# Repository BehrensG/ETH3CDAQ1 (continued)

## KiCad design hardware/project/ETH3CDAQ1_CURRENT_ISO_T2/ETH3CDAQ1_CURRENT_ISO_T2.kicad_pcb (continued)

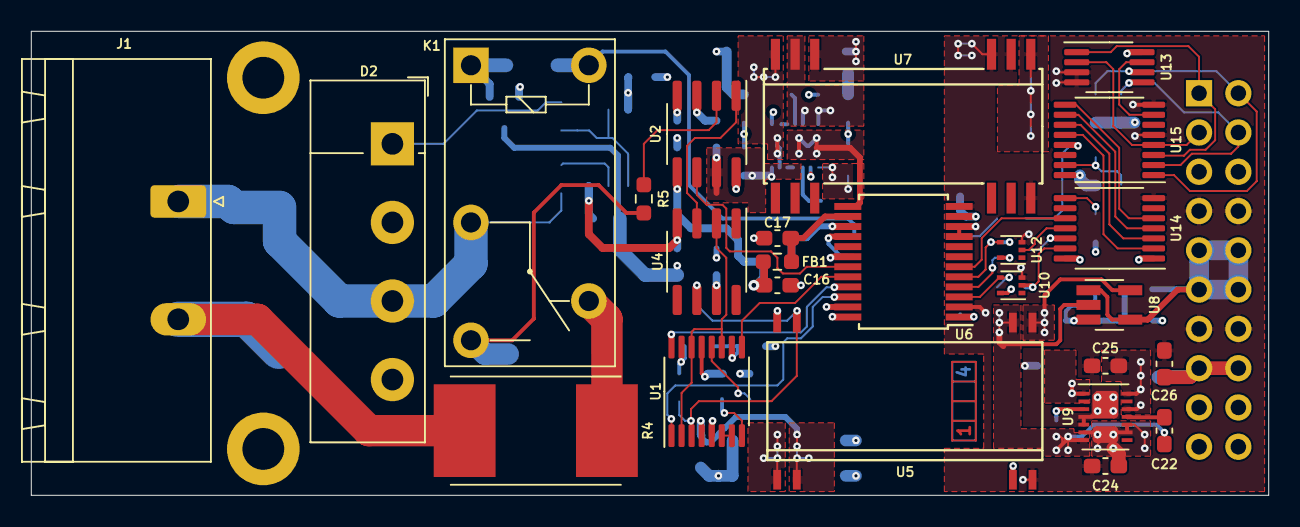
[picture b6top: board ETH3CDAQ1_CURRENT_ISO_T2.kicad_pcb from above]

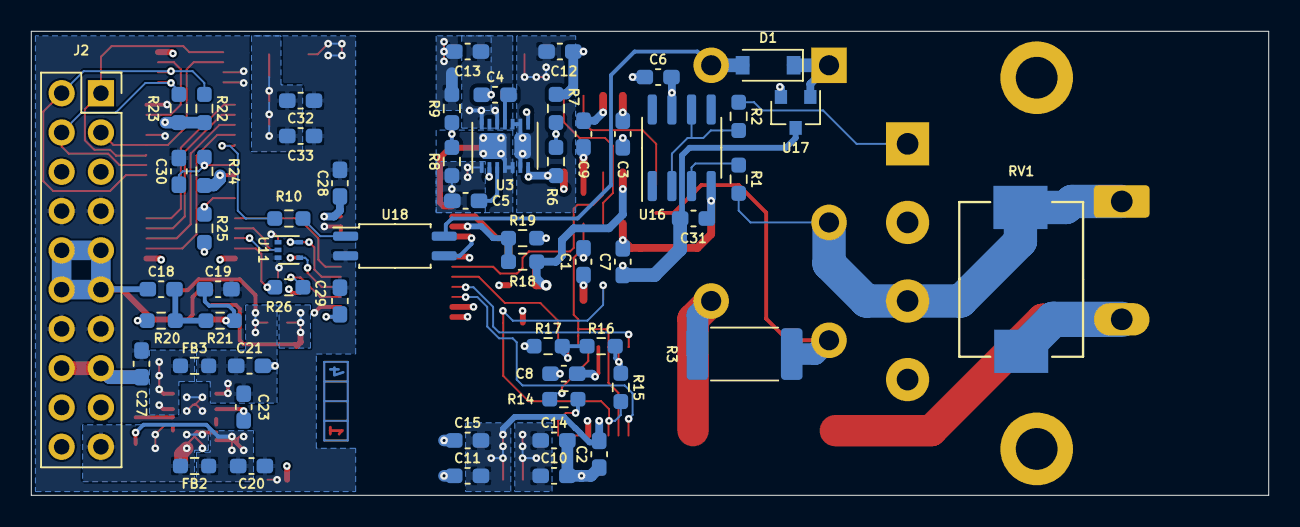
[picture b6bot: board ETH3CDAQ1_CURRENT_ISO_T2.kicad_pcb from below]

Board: 4 copper layers, 80.0 x 30.0 mm, 85 parts (58 on the bottom side), 65 nets.

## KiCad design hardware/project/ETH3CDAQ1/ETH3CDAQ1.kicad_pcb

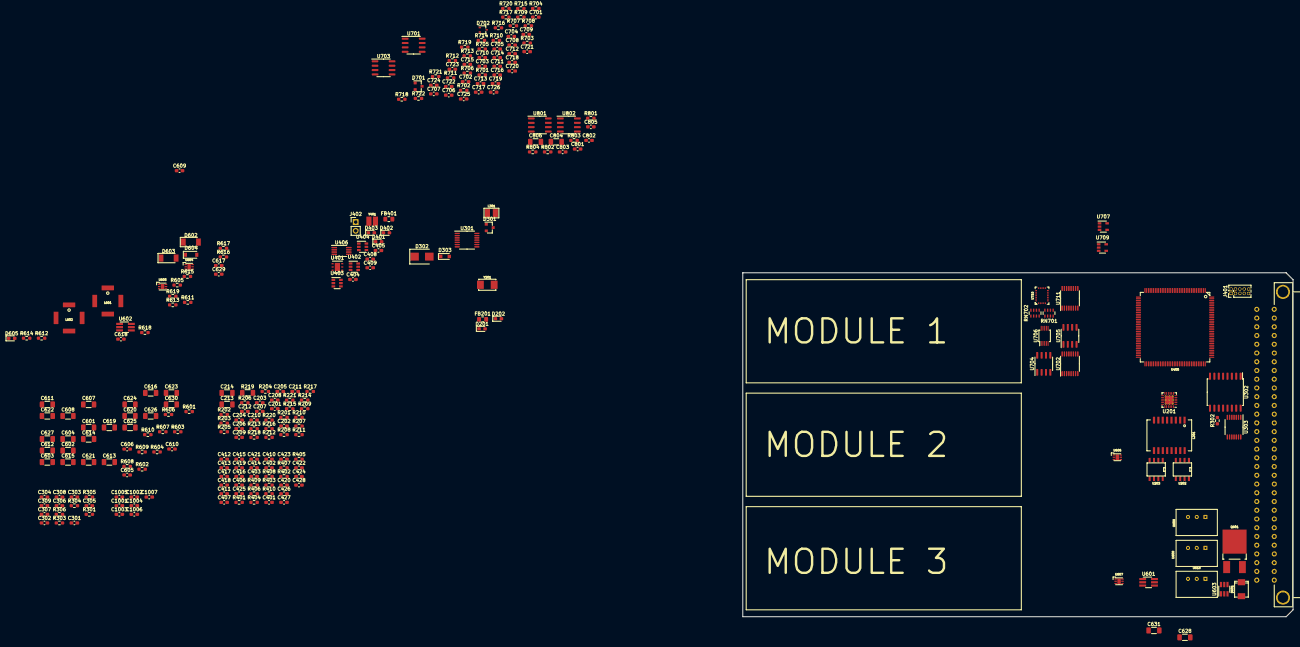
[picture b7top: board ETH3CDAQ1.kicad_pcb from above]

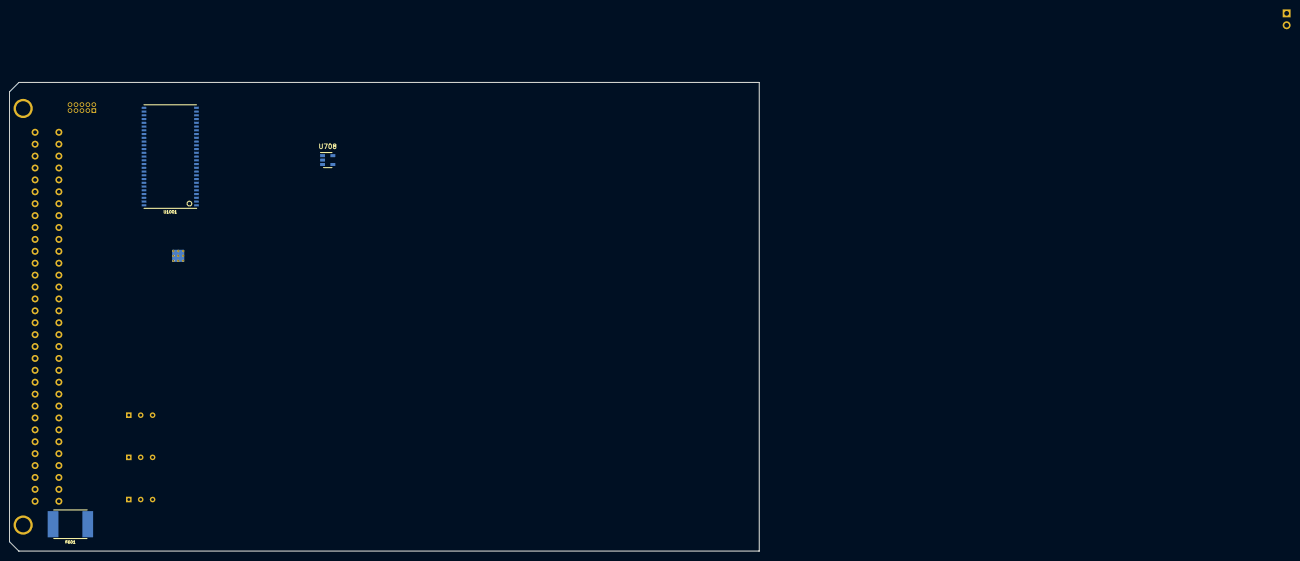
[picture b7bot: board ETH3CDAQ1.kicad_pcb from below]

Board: 4 copper layers, 160.0 x 100.0 mm, 269 parts (3 on the bottom side), 207 nets, no tracks yet.

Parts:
C201, C204, C404, C405: 8p; C_0603_1608Metric_Pad1.08x0.95mm_HandSolder
C202, C205, C208, C209, C210, C211, C212, C301, C303, C304, C306, C308, C401, C402, C403, C406, C407, C411, C412, C413, C414, C415, C416, C417, C418, C419, C420, C421, C422, C423, C424, C425, C426, C428, C617, C618, C629, C701, C702, C703, C704, C705, C706, C707, C708, C709, C710, C712, C713, C714, C715, C717, C718, C719, C720, C722, C801, C802, C803, C805, C1001, C1002, C1003, C1004, C1005, C1006, C1007: 100n; C_0603_1608Metric_Pad1.08x0.95mm_HandSolder
C203: 470p; C_0603_1608Metric_Pad1.08x0.95mm_HandSolder
C206, C207, C302, C305, C307, C410, C427, C605, C606: 1u; C_0603_1608Metric_Pad1.08x0.95mm_HandSolder
C213, C214: 1n/1kV; C_1206_3216Metric_Pad1.33x1.80mm_HandSolder
C309, C724: 47p; C_0603_1608Metric_Pad1.08x0.95mm_HandSolder
C408, C409, C723: 2u2; C_0603_1608Metric_Pad1.08x0.95mm_HandSolder
C601, C602, C615, C616, C623, C624, C628: 10u/50V; C_1206_3216Metric_Pad1.33x1.80mm_HandSolder
C603, C604, C611, C612, C613, C614: 4u7/50V; C_1206_3216Metric_Pad1.33x1.80mm_HandSolder
C607, C608: 1u/HC; C_1206_3216Metric_Pad1.33x1.80mm_HandSolder
C609, C610: 4p7; C_0603_1608Metric_Pad1.08x0.95mm_HandSolder
C619, C620: 10u/35V; C_1206_3216Metric_Pad1.33x1.80mm_HandSolder
C621: 4u7/25V; C_1206_3216Metric_Pad1.33x1.80mm_HandSolder
C622, C804, C806: 10u; C_1206_3216Metric_Pad1.33x1.80mm_HandSolder
C625, C626, C630, C631: 10u/16V; C_1206_3216Metric_Pad1.33x1.80mm_HandSolder
C627: 4u7; C_1206_3216Metric_Pad1.33x1.80mm_HandSolder
C711: 330p; C_0603_1608Metric_Pad1.08x0.95mm_HandSolder
C716: 100p; C_0603_1608Metric_Pad1.08x0.95mm_HandSolder
C721: 1000p; C_0603_1608Metric_Pad1.08x0.95mm_HandSolder
C725, C726: C; C_0603_1608Metric_Pad1.08x0.95mm_HandSolder
D201: YELLOW; LED_0603_1608Metric_Pad1.05x0.95mm_HandSolder
D202, D402: GREEN; LED_0603_1608Metric_Pad1.05x0.95mm_HandSolder
D301: BAV99; SOT-23
D302: SMBJ5.0A; D_SMB
D303: SD36C-01FTG; D_SOD-323_HandSoldering
D401, D605: RED; LED_0603_1608Metric_Pad1.05x0.95mm_HandSolder
D403: BLUE; LED_0603_1608Metric_Pad1.05x0.95mm_HandSolder
D601: SM6T30AY; DO_214AA_REV
D602, D603: PMEG6010EP,115; D_SOD-128
D604: MMSZ5249B; D_SOD-123
D701: MMBZ15VDL; SOT-23
D702: BAT54SW; SOT-323_SC-70
F601: MF-LSMF185/33X; Fuse_SMD2920
FB201, FB401: 742792031; L_0805_2012Metric_Pad1.15x1.40mm_HandSolder
J401: 20021111-00010T4LF; PinHeader_2x05_P1.27mm_Vertical
J402: Conn_02x01; PinHeader_1x02_P2.54mm_Vertical
J501: C64AC; Socket_DIN41612-CaseC1-AC-Male-64Pin-2rows
L201: 749010012A
L301: CW252016-R33G; CW252016
L601, L602: 74489440068
Q601: IRFR5410; TO-252-2_Rectifier
R201, R202, R204, R205: 33; R_0603_1608Metric_Pad0.98x0.95mm_HandSolder
R203, R206, R207, R208, R209, R211, R301, R408, R409, R410, R705, R706, R707, R801, R802, R804: 10k; R_0603_1608Metric_Pad0.98x0.95mm_HandSolder
R210: 1k5; R_0603_1608Metric_Pad0.98x0.95mm_HandSolder
R212: 12k1; R_0603_1608Metric_Pad0.98x0.95mm_HandSolder
R213, R214: 270; R_0603_1608Metric_Pad0.98x0.95mm_HandSolder
R215, R216, R217, R218: 49R9; R_0603_1608Metric_Pad0.98x0.95mm_HandSolder
R219: 1M/1kV; R_1206_3216Metric_Pad1.30x1.75mm_HandSolder
R220, R221: 75/1%; R_0603_1608Metric_Pad0.98x0.95mm_HandSolder
R302: 14k7; R_0603_1608Metric_Pad0.98x0.95mm_HandSolder
R303: 100; R_0603_1608Metric_Pad0.98x0.95mm_HandSolder
R304: 1k; R_0603_1608Metric_Pad0.98x0.95mm_HandSolder
R305: 47; R_0603_1608Metric_Pad0.98x0.95mm_HandSolder
R306: 51R1; R_0603_1608Metric_Pad0.98x0.95mm_HandSolder
R401, R402, R406, R407: 4k7; R_0603_1608Metric_Pad0.98x0.95mm_HandSolder
R403, R405: 680; R_0603_1608Metric_Pad0.98x0.95mm_HandSolder
R404: 560; R_0603_1608Metric_Pad0.98x0.95mm_HandSolder
R601, R603, R606, R608: 1M; R_0603_1608Metric_Pad0.98x0.95mm_HandSolder
R602, R604: 287k; R_0603_1608Metric_Pad0.98x0.95mm_HandSolder
R605, R611: 100k; R_0603_1608Metric_Pad0.98x0.95mm_HandSolder
R607: 111k; R_0603_1608Metric_Pad0.98x0.95mm_HandSolder
R609: 53k; R_0603_1608Metric_Pad0.98x0.95mm_HandSolder
R610: 370; R_0603_1608Metric_Pad0.98x0.95mm_HandSolder
R612, R618: 49k9; R_0603_1608Metric_Pad0.98x0.95mm_HandSolder
R613: 150k; R_0603_1608Metric_Pad0.98x0.95mm_HandSolder
R614: 13k3; R_0603_1608Metric_Pad0.98x0.95mm_HandSolder
R615, R616, R619: R; R_0603_1608Metric_Pad0.98x0.95mm_HandSolder
R617: 25k; R_0603_1608Metric_Pad0.98x0.95mm_HandSolder
R701, R704, R714: 0; R_0603_1608Metric_Pad0.98x0.95mm_HandSolder
R702, R715: DNP; R_0603_1608Metric_Pad0.98x0.95mm_HandSolder
R703: OPT; R_0603_1608Metric_Pad0.98x0.95mm_HandSolder
R708, R710: 6k81; R_0603_1608Metric_Pad0.98x0.95mm_HandSolder
R709: 11k3; R_0603_1608Metric_Pad0.98x0.95mm_HandSolder
R711, R713: 5k23; R_0603_1608Metric_Pad0.98x0.95mm_HandSolder
R712: 10k2; R_0603_1608Metric_Pad0.98x0.95mm_HandSolder
R716, R717, R718, R719, R720, R721, R722: 620; R_0603_1608Metric_Pad0.98x0.95mm_HandSolder
R803: 20k; R_0603_1608Metric_Pad0.98x0.95mm_HandSolder
RN701, RN702: 1k; R_Array_Concave_4x0603
U201: LAN8742A; QFN-24-1EP_4x4mm_P0.5mm_EP2.6x2.6mm_ThermalVias
U202, U203: LC03-3.3; SO8E
U301: TXB0104PW; TSSOP-14_4.4x5mm_P0.65mm
U302: ADuM5402; SOIC-16W_7.5x10.3mm_P1.27mm
U303: 74AC125; TSSOP-14_4.4x5mm_P0.65mm
U401: HDC1080; Texas_PWSON-N6
U402, U403, U404: SN74LVC1T45DBV; SOT-23-6
U405: STM32H743ZI; TQFP-144_20x20mm_P0.5mm
U406: 24LC08B-E/MS; MSOP-8_3x3mm_P0.65mm
U601, U602: LT8330_S6; TSOT-23-6_HandSoldering
U603: MAX5902; SOT-23-6_Handsoldering
U604, U606: ADP7118_LFCSP6; LFCSP-6_2x2mm_1EP_P0.65mm
U605: ADP7182_LFCSP6; LFCSP-6_2x2mm_1EP_P0.65mm
U607: ADP7182-2V5_LFCSP6; LFCSP-6_2x2mm_1EP_P0.65mm
U608: TSR1-2433; TSR1
U609: TSR1-2450; TSR1
U610: TSR1-2490; TSR1
U701: LT1355; SOIC-8_3.9x4.9mm_P1.27mm
U702: DG211; TSSOP-16_4.4x5mm_P0.65mm
U703, U705: DG419LDY; SOIC-8_3.9x4.9mm_P1.27mm
U704: OPA140; SOIC-8_3.9x4.9mm_P1.27mm
U706: AD8251; MSOP-10_3x3mm_P0.5mm
U707, U708, U709: SN74LVC1G14DBVR; SOT-23-5
U710: ADAQ798x; LGA-24_5x4mm_P0.5mm
U711: 74HCT595; TSSOP-16_4.4x5mm_P0.65mm
U801: OPA2277; SOIC-8_3.9x4.9mm_P1.27mm
U802: ADR4550; SOIC-8_3.9x4.9mm_P1.27mm
U1001: IS42S16400J-xC; TSSOP-54
Y201: NX5032GA-25.000M-LN-CD-1; NX5032GA
Y401: NX3225GD-8MHZ; NX3225GD

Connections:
+3V3: C202.1, C205.1, C301.1, C302.1, C401.1, C402.1, C403.1, C406.1, C407.1, C410.1, C412.1, C414.1, C416.1, C417.1, C418.1, C419.1, C420.1, C421.1, C422.1, C423.1, C424.1, C425.1, C426.1, C625.1, C1001.1, C1002.1, C1003.1, C1004.1, C1005.1, C1006.1, C1007.1, D401.2, D402.2, D403.2, FB201.2, FB401.2, J401.1, R206.1, R207.1, R208.1, R209.1, R210.1, R301.1, R401.1, R402.1, R406.1, R407.1, R409.1, R410.2, U201.9, U301.1, U401.5, U402.6, U403.6, U404.6, U405.6, U405.17, U405.30, U405.39, U405.52, U405.62, U405.72, U405.84, U405.95, U405.108, U405.121, U405.131, U405.143, U405.144, U406.8, U608.3, U710.17, U1001.1, U1001.3, U1001.9, U1001.14, U1001.27, U1001.43, U1001.49
+5V: C303.1, C304.1, C305.1, C411.1, C413.1, C415.1, C626.1, C702.1, C704.1, C706.1, C708.1, C710.1, C713.1, C715.1, C718.1, C723.1, U301.14, U302.1, U402.1, U403.1, U404.1, U609.3, U702.12, U703.5, U705.5, U707.5, U708.5, U709.5, U710.19, U710.20, U711.10, U711.16
+5VP: C805.1, C806.1, R801.2, RN702.8, U801.5, U802.6
+5V_TRIG: C306.1, C307.1, C308.1, R304.1, U302.10, U302.16, U303.14
+7.5V: C629.1, C630.1, C803.1, C804.1, R617.1, U606.1, U710.10, U710.11, U710.21, U802.2
+9V: C621.1, C631.1, U606.4, U606.6, U610.3
+10V: R706.2, R804.1, U801.7
+15V: C617.1, C619.1, C712.1, C714.1, C717.1, C719.1, C722.1, C801.1, R611.1, U604.1, U701.8, U702.13, U703.4, U704.7, U705.4, U706.8, U801.8
+24V: F601.2, J501.A31, J501.A32, J501.C31, J501.C32
+24VF: C601.1, C602.1, C603.1, C604.1, C623.1, C624.1, C628.1, D604.1, L601.1, L602.1, Q601.2, R601.1, R603.1, U601.6, U602.6, U603.2, U608.1, U609.1, U610.1
-2V5: C627.1, C720.1, U607.1, U710.8
-5V: C622.1, U607.3, U607.6, U607.7
-10V: R707.2, R803.1, U801.1
-15V: C618.1, C620.1, C701.1, C703.1, C705.1, C707.1, C709.1, C802.1, R613.1, U605.1, U701.4, U702.4, U703.7, U704.4, U705.7, U706.3, U706.6, U801.4
/Channel 1/CH1_A0: R717.2, U708.2
/Channel 1/CH1_A1: R716.2, U707.2
/Channel 1/CH1_CNV: U405.110, U710.13
/Channel 1/CH1_M_GND: R719.2, U702.16
/Channel 1/CH1_M_IN: R718.2, U702.1
/Channel 1/CH1_M_LPF: R722.2, U709.2
/Channel 1/CH1_M_N10V: R721.2, U702.8
/Channel 1/CH1_M_P10V: R720.2, U702.9
/Channel 1/CH1_SCK: U405.111, U710.15
/Channel 1/CH1_SDI: U405.116, U710.16
/Channel 1/CH1_SDO: U405.112, U710.14
/Channel 1/LPF: U703.6, U705.6, U709.4
/Channel 1/REF_OUT: D702.2, U710.24
/Connector/EXT_TRIG: C309.1, D303.1, J501.A16, L301.1
/Connector/RX+: J501.A20, U203.8
/Connector/RX-: J501.A21, U203.5
/Connector/TX+: J501.C20, U202.8
/Connector/TX-: J501.C21, U202.5
/Ethernet/ETH_RXN: L201.8, R218.2, U201.22
/Ethernet/ETH_RXP: L201.6, R217.2, U201.23
/Ethernet/ETH_TXN: L201.3, R216.2, U201.20
/Ethernet/ETH_TXP: L201.1, R215.2, U201.21
/Ethernet/MODE0: R201.1, R206.2, U201.8
/Ethernet/MODE1: R202.1, R207.2, U201.7
/Ethernet/MODE2: R204.1, R208.2, U201.11
/Ethernet/NRST: C428.1, J401.10, R409.2, U201.15, U405.25
/Ethernet/REFCLK0: R205.1, R209.2, U201.14
/Ethernet/REF_CLK: R205.2, U405.35
/Ethernet/RMII_CRS_DV: R204.2, U405.43
/Ethernet/RMII_MDC: U201.13, U405.27
/Ethernet/RMII_MDIO: R210.2, U201.12, U405.36
/Ethernet/RMII_RXD0: R201.2, U405.44
/Ethernet/RMII_RXD1: R202.2, U405.45
/Ethernet/RMII_TXD0: U201.17, U405.128
/Ethernet/RMII_TXD1: U201.18, U405.129
/Ethernet/RMII_TXEN: U201.16, U405.126
/MCU/A0: U405.10, U1001.23
/MCU/A1: U405.11, U1001.24
/MCU/A2: U405.12, U1001.25
/MCU/A3: U405.13, U1001.26
/MCU/A4: U405.14, U1001.29
/MCU/A5: U405.15, U1001.30
/MCU/A6: U405.50, U1001.31
/MCU/A7: U405.53, U1001.32
/MCU/A8: U405.54, U1001.33
/MCU/A9: U405.55, U1001.34
/MCU/A10: U405.56, U1001.22
/MCU/A11: U405.57, U1001.35
/MCU/BA0: U405.89, U1001.20
/MCU/BA1: U405.90, U1001.21
/MCU/CKE: U405.135, U1001.37
/MCU/CLK: U405.93, U1001.38
/MCU/D0: U405.85, U1001.2
/MCU/D1: U405.86, U1001.4
/MCU/D2: U405.114, U1001.5
/MCU/D3: U405.115, U1001.7
/MCU/D4: U405.58, U1001.8
/MCU/D5: U405.59, U1001.10
/MCU/D6: U405.60, U1001.11
/MCU/D7: U405.63, U1001.13
/MCU/D8: U405.64, U1001.42
/MCU/D9: U405.65, U1001.44
/MCU/D10: U405.66, U1001.45
/MCU/D11: U405.67, U1001.47
/MCU/D12: U405.68, U1001.48
/MCU/D13: U405.77, U1001.50
/MCU/D14: U405.78, U1001.51
/MCU/D15: U405.79, U1001.53
/MCU/EEPROM_SCL: R407.2, U405.81, U406.6
/MCU/EEPROM_SDA: R406.2, U405.82, U406.5
/MCU/EEPROM_WP: U405.80, U406.7
/MCU/LDQM: U405.141, U1001.15
/MCU/MCU_SR_CLK: U403.4, U405.97
/MCU/MCU_SR_DAT: U402.4, U405.96
/MCU/MCU_SR_LAT: U404.4, U405.98
/MCU/MCU_VDDA: C427.1, FB401.1, U405.32, U405.33
/MCU/SD_CLK: U403.3, U711.11
/MCU/SD_DAT: U402.3, U711.14
/MCU/SD_LAT: U404.3, U711.12
/MCU/SENS_SCL: R401.2, U401.6, U405.100
/MCU/SENS_SDA: R402.2, U401.1, U405.99
/MCU/TCK_SWCLK: J401.4, U405.109
/MCU/TMS_SWDIO: J401.2, U405.105
/MCU/TRIG_EN: U301.2, U405.73
/MCU/TRIG_IN: U301.4, U405.69
/MCU/TRIG_OUT: U301.3, U405.70
/MCU/UDQM: U405.142, U1001.39
/MCU/~CAS: U405.132, U1001.17
/MCU/~CS: U405.136, U1001.19
/MCU/~RAS: U405.49, U1001.18
/MCU/~WE: U405.26, U1001.16
/Trigger/EXT_TRIG_SIGN: R302.1, U302.12, U303.3
/Trigger/TRIG_OUT_EN: U302.14, U303.4, U303.10, U303.13
/Trigger/TRIG_OUT_SIGN: U302.13, U303.5, U303.9, U303.12
Earth: C213.1, C214.2, J501.A18, J501.A22, J501.C18, J501.C22, R219.1
GND: C201.2, C202.2, C203.2, C204.2, C205.2, C206.2, C207.2, C208.2, C209.2, C210.2, C211.2, C212.2, C213.2, C301.2, C302.2, C303.2, C304.2, C305.2, C401.2, C402.2, C403.2, C404.2, C405.2, C406.2, C407.2, C408.2, C409.2, C410.2, C411.2, C412.2, C413.2, C414.2, C415.2, C416.2, C417.2, C418.2, C419.2, C420.2, C421.2, C422.2, C423.2, C424.2, C425.2, C426.2, C427.2, C428.2, C601.2, C602.2, C603.2, C604.2, C605.2, C606.2, C611.2, C612.2, C613.2, C614.2, C615.2, C616.2, C619.2, C620.2, C621.2, C622.2, C623.2, C624.2, C625.2, C626.2, C627.2, C628.2, C630.2, C631.2, C1001.2, C1002.2, C1003.2, C1004.2, C1005.2, C1006.2, C1007.2, D601.2, D602.1, D605.1, J401.3, J401.5, J402.2, J501.A27, J501.A28, J501.C27, J501.C28, R203.2, R211.2, R212.1, R213.2, R214.2, R219.2, R408.2, R602.2, R604.2, R607.2, R609.2, R612.2, R614.2, R618.2, U201.25, U301.7, U302.2, U302.8, U401.2, U402.2, U402.5, U403.2, U403.5, U404.2, U404.5, U405.16, U405.31, U405.38, U405.51, U405.61, U405.83, U405.94, U405.107, U405.120, U405.130, U406.1, U406.2, U406.3, U406.4, U601.2, U602.2, U603.4, U604.3, U604.7, U605.5, U606.3, U606.7, U607.5, U608.2, U609.2, U610.2, U702.5, U703.3, U705.3, U711.13, U1001.6, U1001.12, U1001.28, U1001.41, U1001.46, U1001.52, U1001.54
GNDA: C701.2, C702.2, C703.2, C704.2, C705.2, C706.2, C707.2, C708.2, C709.2, C710.2, C711.2, C712.2, C713.2, C714.2, C715.2, C717.2, C718.2, C719.2, C720.2, C721.2, C722.2, C723.2, C725.2, C801.2, C802.2, C803.2, C804.2, C805.2, C806.2, D701.1, D702.1, R702.2, R705.2, R715.1, R802.2, RN702.4, U701.3, U701.5, U706.1, U706.2, U706.9, U707.3, U708.3, U709.3, U710.4, U710.5, U710.6, U710.7, U710.9, U710.18, U710.22, U711.8, U801.3, U802.4
GND_TRIG: C306.2, C307.2, C308.2, D301.1, D302.2, D303.2, J501.C16, R306.2, U302.9, U302.15, U303.1, U303.7
unnamed: C201.1, U201.5, Y201.2
unnamed: C203.1, C206.1, U201.6
unnamed: C204.1, U201.4, Y201.1
unnamed: C214.1, R220.2, R221.2
unnamed: C309.2, R306.1
unnamed: C404.1, U405.23, Y401.1
unnamed: C405.1, U405.24, Y401.2
unnamed: C408.1, U405.71
unnamed: C409.1, U405.106
unnamed: C605.1, U601.5
unnamed: C606.1, U602.5
unnamed: C607.1, D603.2, L601.2
unnamed: C607.2, L601.4, U601.1
unnamed: C608.1, D602.2, L602.2
unnamed: C608.2, L602.4, U602.1
unnamed: C609.1, C611.1, C613.1, C615.1, D603.1, R606.1, U604.4, U604.6
unnamed: C609.2, R606.2, R607.1, U601.3
unnamed: C610.1, C612.1, C614.1, C616.1, L602.3, R608.1, U605.3, U605.6, U605.7
unnamed: C610.2, R608.2, R609.1, U602.3
unnamed: C617.2, R615.1
unnamed: C618.2, R616.1
unnamed: C629.2, R619.1
unnamed: C711.1, R708.1, R709.2, R710.2
unnamed: C716.1, R710.1, R711.2, U701.1
unnamed: C716.2, R709.1, U701.2
unnamed: C721.1, R711.1, R712.2, R713.2
unnamed: C724.1, R713.1, U701.7, U705.8
unnamed: C724.2, R712.1, U701.6
unnamed: C725.1, RN702.5, RN702.6, RN702.7, U710.1
unnamed: C726.1, D702.3, RN701.5, RN701.6, U710.3
unnamed: C726.2, RN701.3, RN701.4, RN701.7, U710.2
unnamed: D201.1, R213.1
unnamed: D201.2, R211.1, U201.2
unnamed: D202.1, R214.1
unnamed: D202.2, U201.3
unnamed: D301.2, D302.1, R304.2
unnamed: D301.3, R303.2, R305.1, U303.6, U303.8, U303.11
unnamed: D401.1, R403.2
unnamed: D402.1, R404.2
unnamed: D403.1, R405.2
unnamed: D601.1, F601.1, Q601.3, R605.1, U603.1
unnamed: D604.2, R610.1
unnamed: D605.2, R610.2
unnamed: D701.2, R701.1, R702.1, R703.2, U704.3
unnamed: J402.1, R410.1, U405.46
unnamed: L201.9, U203.4
unnamed: L201.10, R220.1
unnamed: L201.11, U203.1
unnamed: L201.14, U202.4
unnamed: L201.15, R221.1
unnamed: L201.16, U202.1
unnamed: L301.2, R305.2
unnamed: Q601.1, U603.3
unnamed: R203.1, U201.10
unnamed: R212.2, U201.24
unnamed: R301.2, U301.8
unnamed: R302.2, R303.1, U303.2
unnamed: R403.1, U405.7
unnamed: R404.1, U405.8
unnamed: R405.1, U405.9
unnamed: R408.1, U405.138
unnamed: R601.2, R602.1, U601.4
unnamed: R603.2, R604.1, U602.4
unnamed: R605.2, U603.6
unnamed: R611.2, R612.1, R615.2, U604.2
unnamed: R613.2, R614.1, R616.2, U605.2
unnamed: R617.2, R618.1, R619.2, U606.2
unnamed: R703.1, R704.2, U704.2, U704.6
unnamed: R704.1, U702.2
unnamed: R705.1, U702.14
unnamed: R706.1, U702.11
unnamed: R707.1, U702.7
unnamed: R708.2, U703.8
unnamed: R714.1, R715.2, U706.10
unnamed: R714.2, U705.1
unnamed: R716.1, U711.15
unnamed: R717.1, U711.1
unnamed: R718.1, U711.2
unnamed: R719.1, U711.3
unnamed: R720.1, U711.4
unnamed: R721.1, U711.5
unnamed: R722.1, U711.6
unnamed: R801.1, R803.2, U801.2
unnamed: R802.1, R804.2, U801.6
unnamed: RN701.1, U706.7
unnamed: RN701.2, RN701.8
unnamed: RN702.1, RN702.2, RN702.3
unnamed: U301.11, U302.5
unnamed: U301.12, U302.4
unnamed: U301.13, U302.3
unnamed: U702.3, U702.6, U702.10, U702.15, U703.1
unnamed: U703.2, U705.2
unnamed: U706.4, U708.4
unnamed: U706.5, U707.4
VCCQ: C207.1, C208.1, C209.1, C210.1, C211.1, C212.1, FB201.1, L201.2, L201.7, R215.1, R216.1, R217.1, R218.1, U201.1, U201.19

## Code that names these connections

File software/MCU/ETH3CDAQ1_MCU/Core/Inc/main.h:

/* USER CODE BEGIN Header */
/**
  ******************************************************************************
  * @file           : main.h
  * @brief          : Header for main.c file.
  *                   This file contains the common defines of the application.
  ******************************************************************************
  * @attention
  *
  * <h2><center>&copy; Copyright (c) 2020 STMicroelectronics.
  * All rights reserved.</center></h2>
  *
  * This software component is licensed by ST under BSD 3-Clause license,
  * the "License"; You may not use this file except in compliance with the
  * License. You may obtain a copy of the License at:
  *                        opensource.org/licenses/BSD-3-Clause
  *
  ******************************************************************************
  */
/* USER CODE END Header */

/* Define to prevent recursive inclusion -------------------------------------*/
#ifndef __MAIN_H
#define __MAIN_H

#ifdef __cplusplus
extern "C" {
#endif

/* Includes ------------------------------------------------------------------*/
#include "stm32h7xx_hal.h"

#include "stm32h7xx_ll_system.h"
#include "stm32h7xx_ll_gpio.h"
#include "stm32h7xx_ll_exti.h"
#include "stm32h7xx_ll_bus.h"
#include "stm32h7xx_ll_cortex.h"
#include "stm32h7xx_ll_rcc.h"
#include "stm32h7xx_ll_utils.h"
#include "stm32h7xx_ll_pwr.h"
#include "stm32h7xx_ll_dma.h"

/* Private includes ----------------------------------------------------------*/
/* USER CODE BEGIN Includes */

/* USER CODE END Includes */

/* Exported types ------------------------------------------------------------*/
/* USER CODE BEGIN ET */

/* USER CODE END ET */

/* Exported constants --------------------------------------------------------*/
/* USER CODE BEGIN EC */

/* USER CODE END EC */

/* Exported macro ------------------------------------------------------------*/
/* USER CODE BEGIN EM */

/* USER CODE END EM */

/* Exported functions prototypes ---------------------------------------------*/
void Error_Handler(void);

/* USER CODE BEGIN EFP */

/* USER CODE END EFP */

/* Private defines -----------------------------------------------------------*/
#define SR_DAT_Pin LL_GPIO_PIN_2
#define SR_DAT_GPIO_Port GPIOE
#define SR_LAT_Pin LL_GPIO_PIN_3
#define SR_LAT_GPIO_Port GPIOE
#define SR_CLK_Pin LL_GPIO_PIN_4
#define SR_CLK_GPIO_Port GPIOE
#define DAC_nSYNC_Pin LL_GPIO_PIN_6
#define DAC_nSYNC_GPIO_Port GPIOF
#define DAC_SCLK_Pin LL_GPIO_PIN_7
#define DAC_SCLK_GPIO_Port GPIOF
#define SPI5_NOT_USED_Pin LL_GPIO_PIN_8
#define SPI5_NOT_USED_GPIO_Port GPIOF
#define DAC_DIN_Pin LL_GPIO_PIN_9
#define DAC_DIN_GPIO_Port GPIOF
#define DAC_LDAC_Pin LL_GPIO_PIN_10
#define DAC_LDAC_GPIO_Port GPIOF
#define TRIG_EN_Pin LL_GPIO_PIN_4
#define TRIG_EN_GPIO_Port GPIOA
#define TRIG_OUT_Pin LL_GPIO_PIN_5
#define TRIG_OUT_GPIO_Port GPIOA
#define TRIG_IN_Pin LL_GPIO_PIN_6
#define TRIG_IN_GPIO_Port GPIOA
#define TRIG_IN_EXTI_IRQn EXTI9_5_IRQn
#define MCU_DEFAULT_Pin LL_GPIO_PIN_0
#define MCU_DEFAULT_GPIO_Port GPIOB
#define LED_RED_Pin LL_GPIO_PIN_12
#define LED_RED_GPIO_Port GPIOB
#define EEPROM_WP_Pin LL_GPIO_PIN_11
#define EEPROM_WP_GPIO_Port GPIOD
#define EEPROM_SCL_Pin LL_GPIO_PIN_12
#define EEPROM_SCL_GPIO_Port GPIOD
#define EEPROM_SDA_Pin LL_GPIO_PIN_13
#define EEPROM_SDA_GPIO_Port GPIOD
#define LED_GREEN_Pin LL_GPIO_PIN_3
#define LED_GREEN_GPIO_Port GPIOG
#define LED_BLUE_Pin LL_GPIO_PIN_6
#define LED_BLUE_GPIO_Port GPIOG
#define SENS_SDA_Pin LL_GPIO_PIN_9
#define SENS_SDA_GPIO_Port GPIOC
#define SENS_SCL_Pin LL_GPIO_PIN_8
#define SENS_SCL_GPIO_Port GPIOA
#define MCU_nCS_Pin LL_GPIO_PIN_15
#define MCU_nCS_GPIO_Port GPIOA
#define MCU_CLK_Pin LL_GPIO_PIN_10
#define MCU_CLK_GPIO_Port GPIOC
#define MCU_MISO_Pin LL_GPIO_PIN_11
#define MCU_MISO_GPIO_Port GPIOC
#define MCU_MOSI_Pin LL_GPIO_PIN_12
#define MCU_MOSI_GPIO_Port GPIOC
/* USER CODE BEGIN Private defines */

/* USER CODE END Private defines */

#ifdef __cplusplus
}
#endif

#endif /* __MAIN_H */

/************************ (C) COPYRIGHT STMicroelectronics *****END OF FILE****/

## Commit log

2020-11-12 Schematic design
2020-11-15 Schematic design.
2020-11-17 PCB layout
2020-11-18 PCB layout.
2020-11-18 Measurement module development.
2020-11-19 Meas. module schematic design.
2020-11-22 PCB design
2020-11-27 Small modification
2020-11-27 Started development of first current measurement module. Added CAN to the DAQ module.
2020-11-28 Voltage front-end development
2020-11-29 Voltage module done.
2020-11-30 Current module development.
2020-11-30 Modifications in PCBs.
2020-12-01 Current module development
2020-12-03 Added selftest circuit in the base PCB.
2020-12-04 PCB design.
2020-12-04 Revert "PCB design"
    This reverts commit 7e60bb31762e39c58652df4eecb6f638629803d3.
2020-12-04 Revert "Revert "PCB design""
    This reverts commit e51338887ee5d44a68eac03a1fbbc2a91ecb03d8.
2020-12-06 PCB design done
2020-12-07 Modifications in PCB and schematic in the base module.
2020-12-07 Base module PCB modifications.
2020-12-11 Modification in PCBs. Created BOM files.
2020-12-12 Modification in measurement module PCB.
2020-12-14 Development of new measurement module. High precision ADC.
2020-12-16 PCB modifications
2020-12-21 Changed Fix.txt
2020-12-21 Token test
2020-12-23 Fixed mistake with DG419. Never use DG419Lxx variant.
2020-12-27 STM32H7+FreeRTOS+LwIP works, thanks to this guide https://community.st.com/s/article/How-to-create-project-for-STM32H7-with-Ethernet-and-LwIP-stack-working. Add a 100ms delay before LWiP Init functio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
2020-12-29 SDRAM works, thanks to the website https://medium.com/@pjinwoo123/stm32h7-external-sdram-evaluation-board-cc72444898d8 . Modified the code to work with SDRAM BANK2. SCPI library works.
2021-01-02 Changed 24LC08 to 24LC024. Added fixes to ethernetif.c to solve the problem with D Cache and RX deadlock. The fixes are also in ethernetif_fix.c, because code generator will overwrite ethernetif.c.
2021-01-05 Added SDRAM to the linker file.
2021-01-10 PCB and software development.
2021-01-15 DAC SPI connection works. Changed ethernetif_fix.c
2021-01-28 Development
2021-02-22 Software development.
2021-02-23 Software develop.
2021-03-22 MCU software development.
2021-06-05 Software development for ADC control.
2021-06-11 Software development
2021-06-15 Software
2021-06-18 Changed SPI3 data size from 8bit to 32bit. Adjusted ADS8681.c code.
2021-06-18 EEPROM function doesn't work for base board and modules.
2021-06-21 Changed EEPROM functions input parameters.
2021-06-21 New SCPI functions.
2021-06-23 Fixed problems with the EEPROM functions.
2021-06-24 Fixed module gain control function.
2021-06-25 Added new SCPI function.
